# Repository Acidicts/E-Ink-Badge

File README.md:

# E-Ink Badge

A DIY Custom Designed, Monochrome, E-Ink display badge powered by the RP2350A, inspired by the GitHub Universe 2024 conference badge.
~Kinda wanted to see how many words I could describe it with. 

<div style="width:100%; display:inline-flex">

</div>

*(Renders made in Fusion 360)*

<div style="width:100%;">
    <div style="width:100%; display:inline-flex">

    </div>
    <div style="width:100%; display:inline-flex">
        
    </div>
</div>

## Features

- **MCU:** The mighty RP2350A I wish the RP2354A were in stock though
- **Flash:** 16MB onboard but do I want it to remember?
- **Power:** Integrated battery management for a single-cell LiPo, does it charge idk
- **Display:** E-Ink support over SPI, this was painful for part selection
- **Software:** No dedicated firmware/software yet — I'm considering adapting the [Badger 2040](https://github.com/pimoroni/badger2040) software from the GitHub Universe conference badge as a starting point, don't have the time for it

## Build Guide

This board has some fine-pitch and hand-soldering-unfriendly parts (the RP2350A and the E-Ink display's FPC connector), so I'd recommend using a **PCBA service** for the main board rather than hand-soldering it yourself. I know I wouldn't I have tried and failed, mainly cuz I dont have a hotplate.

Most components will already be populated(i liked this fancy word better than `placed`) by the assembly service — you'll only need to install the **battery** and the **display** yourself:

**Bring your own adhesive, please**
~ Not on BOM cuz not required for functionality

1. **Prepare the battery connector:** Trim the battery connector's legs slightly so they don't press against the back of the display once everything is assembled.
2. **Mount the battery:** Apply adhesive to the marked area on the PCB and stick the battery down.
3. **Connect the battery:** Plug the battery cable into the battery connector on the PCB.
4. **Mount the display:** Apply adhesive to the marked area on the front of the PCB and attach the E-Ink display. 
5. **Connect the display cable:** Route the ribbon cable through the indentation/slot in the PCB. Open the FPC connector's clamp arm, insert the ribbon cable, then press the clamp lever back down to lock it in place.

"That's it — the badge is fully assembled", I'd like to say, whether the firmware actually works, is what I'd like to know.

For getting started with software, I'd recommend flashing **CircuitPython**, as it's the easiest way to get up and running. Also have some demo firmware included in this repo, though it's untested/may not work out of the box.

## Firmware

I have some basic firmware in this repo. If you'd like to write your own, here are the SPI pin mappings for the display connection:

### SPI Pinout

| Signal | GPIO |
|--------|------|
| SCLK (Clock)      | GPIO 2 |
| SDI (MOSI/Data)   | GPIO 3 |
| D/C (Data/Command)| GPIO 4 |
| CS (Chip Select)  | GPIO 5 |
| RES (Reset)       | GPIO 6 |
| BUSY              | GPIO 7 |

## Bill of Materials (BOM)

- [Project BOM](./BOM.csv) — full parts list for the badge
- [PCB BOM](./PCB_BOM.md) — parts list specific to the PCB assembly

### AI Usage Declaration 
- In part research
- Part finding (lcsc is hit or miss at finding stuff)
- Firmware Demo creation
- README Build Guide (code completion - fancy autocorrect ig)

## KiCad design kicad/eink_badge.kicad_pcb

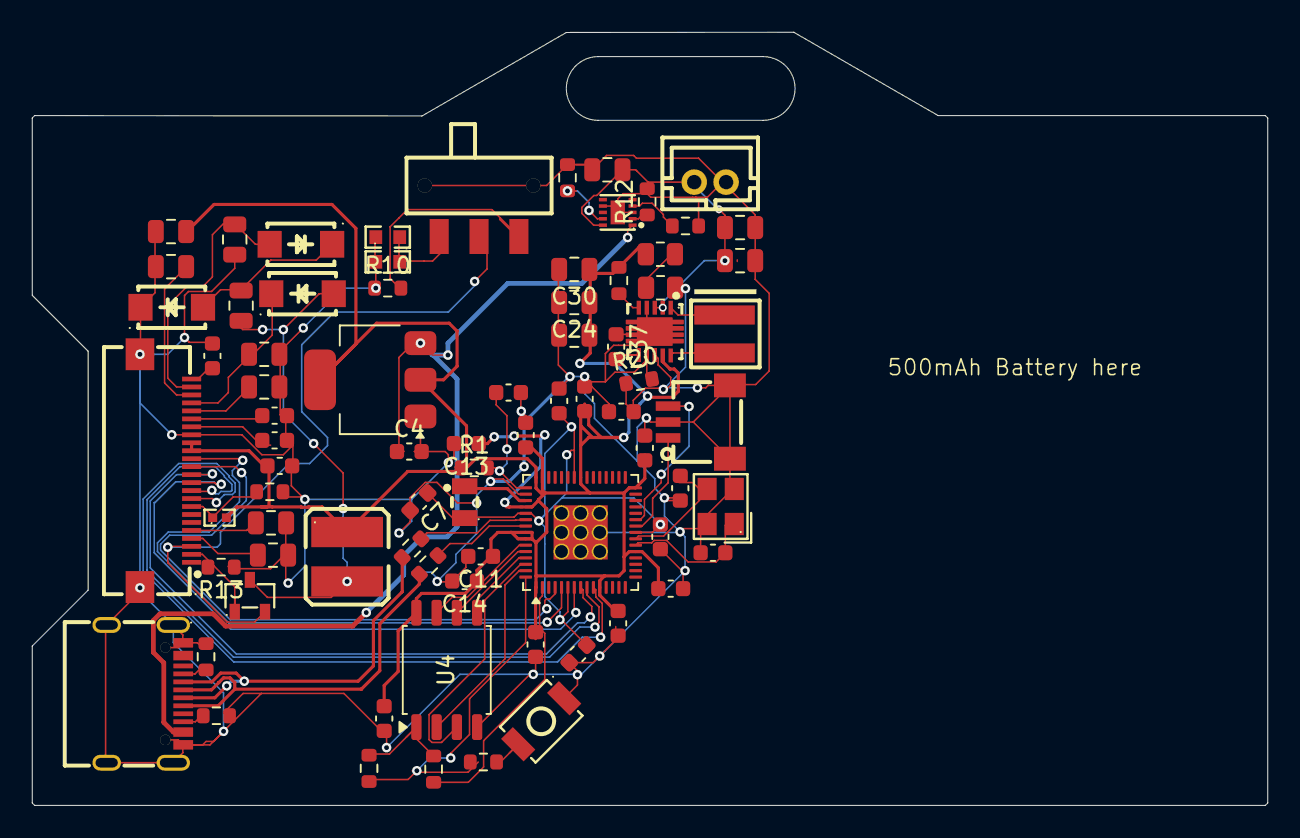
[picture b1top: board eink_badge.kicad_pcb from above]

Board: 2 copper layers, 77.5 x 48.5 mm, 78 parts (0 on the bottom side), 51 nets.

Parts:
C1, C2, C3, C7: 4.7u; C_0603_1608Metric
C4, C5: 10u; C_0603_1608Metric
C6, C8, C9, C10, C11, C12, C13, C14, C15, C16: 100n; C_0603_1608Metric
C17, C18: 15p; C_0603_1608Metric
C19, C20, C21, C22, C23, C25, C26, C27, C29: CL21A475KAQNNNE; C_0805_2012Metric
C24, C30, C35: 22uF; C_0805_2012Metric
C28, C36: 10uF; C_0805_2012Metric
C31, C32, C33, C34: 1uF; C_0603_1608Metric
C37: 0.1uF; C_0603_1608Metric
C38: 10pF; C_0603_1608Metric
CN2: B2B-PH-K-S; CONN-TH_B2B-PH-K-S
D4, D5, D6: SS14; SMA_L4.2-W2.6-LS5.0-RD_1
FPC1: FPC-05FB-24PH20; FPC-SMD_24P-P0.50_FPC-05FB-24PH20
L1: AOTA-B201610S3R3-101-T; IND-SMD_L2.0-W1.6_AOTA-B201610S3R3-101-T
L2: XFL4020-102MEC; IND-SMD_L4.0-W4.0_XFL4020-102MEB
Q1: AO3400A; SOT-23-3_L2.9-W1.3-P1.90-LS2.4-BR
R1: 33; R_0603_1608Metric
R2, R3: 5.1k; R_0603_1608Metric
R4, R5: 27; R_0603_1608Metric
R6: 0; R_0603_1608Metric
R7: DNF; R_0603_1608Metric
R8: 2k; R_0603_1608Metric
R9, R12: 1k; R_0603_1608Metric
R10, R11: 2.2; R_0603_1608Metric
R13, R17: 10k; R_0603_1608Metric
R14: 10k; R0402
R15, R16: 1; R0603
R18: 1M; R_0603_1608Metric
R19, R21: 560k; R_0805_2012Metric
R20: 200k; R_0603_1608Metric
SW1: MST-12D18G2 SMD SLIDE SWITCH; SW-SMD_3P-L9.1-W3.5-P2.50_MST-12D18G2
U1: RP2350A; QFN-60-1EP_7x7mm_P0.4mm_EP3.4x3.4mm
U2: NCP1117-3.3_SOT223; SOT-223-3_TabPin2
U3: GT-USB-7010ASV; USB-C-SMD_G-SWITCH_GT-USB-7010ASV
U4: W25Q128JVS; SOIC-8_5.3x5.3mm_P1.27mm
U5: YZA-009; SW-SMD_YZA-009
U6: ABM8-272-T3_C20625731; CRYSTAL-SMD_4P-L3.2-W2.5-BL
U7: SM03B-SRSS-TB; CONN-SMD_SM03B-SRSS-TB-LF-SN-P
U8: CY43-10UH; IND-SMD_L4.5-W4.0
U9: BQ24040DSQR; WSON-10_L2.0-W2.0-P0.40-BL-EP
U10: TPS63060DSCR; WSON-10_L3.0-W3.0-P0.50-BL-EP-A

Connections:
+1V1: C2.1, C6.1, C7.1, C8.1, L1.1, U1.6 (DVDD), U1.23 (DVDD), U1.39 (DVDD), U1.50 (VREG_FB)
+3V3: C1.1, C5.1, C9.1, C10.1, C11.1, C12.1, C13.1, C14.1, C15.1, C16.1, C24.1, C27.2, C30.1, C34.2, C35.1, FPC1.15, FPC1.16, R1.1, R14.2, R18.1, R21.1, U1.1 (IOVDD), U1.11 (IOVDD), U1.20 (IOVDD), U1.30 (IOVDD), U1.38 (IOVDD), U1.44 (ADC_AVDD), U1.45 (IOVDD), U1.49 (VREG_VIN), U1.53 (USB_OTP_VDD), U1.54 (QSPI_IOVDD), U2.2 (VO), U4.8 (VCC), U8.1, U10.9 (VOUT)
/Battery Charger/Batt+: C23.2, C28.2, C36.2, CN2.2, U9.10 (OUT), U10.2 (VIN), U10.3 (EN)
/E Ink/BS: FPC1.8, R11.1, R14.1
/E Ink/GDR: FPC1.2, Q1.1 (G), R13.2
/E Ink/PREVGH: C20.2, D6.1 (K), FPC1.21
/E Ink/PREVGL: C19.2, D4.2 (A), FPC1.23
/E Ink/RESE: FPC1.3, Q1.2 (S), SW1.2
/E Ink/VCOM: C31.2, FPC1.24
/Root/D+: R5.1, U3.A6 (DP1), U3.B6 (DP2)
/Root/D-: R4.1, U3.A7 (DN1), U3.B7 (DN2)
/Root/GPIO0: R7.1, U1.2 (GPIO0)
/Root/QSPI_SCLK: U1.56 (QSPI_SCLK), U4.6 (CLK)
/Root/QSPI_SD0: U1.57 (QSPI_SD0), U4.5 (DI/IO_{0})
/Root/QSPI_SD1: U1.59 (QSPI_SD1), U4.2 (DO/IO_{1})
/Root/QSPI_SD2: U1.58 (QSPI_SD2), U4.3 (~WP/IO_{2})
/Root/QSPI_SD3: U1.55 (QSPI_SD3), U4.7 (~HOLD/~RESET/IO_{3})
/Root/QSPI_SS: R6.1, R9.2, U1.60 (~QSPI_SS)
/Root/SWCLK: U1.24 (SWCLK), U7.1
/Root/SWDIO: U1.25 (SWDIO), U7.3
/Root/VREG_AVDD: C3.1, R1.2, U1.46 (VREG_AVDD)
/Root/VREG_LX: L1.2, U1.48 (VREG_LX)
/Root/XIN: C18.2, U1.21 (XIN), U6.1
/Root/XOUT: C17.2, U1.22 (XOUT), U6.3
GND: C1.2, C2.2, C3.2, C4.2, C5.2, C6.2, C7.2, C8.2, C9.2, C10.2, C11.2, C12.2, C13.2, C14.2, C15.2, C16.2, C17.1, C18.1, C19.1, C20.1, C22.2, C23.1, C24.2, C25.1, C26.1, C27.1, C28.1, C29.2, C30.2, C31.1, C32.1, C33.1, C34.1, C35.2, C36.1, C37.1, C38.1, CN2.1, D5.1 (K), FPC1.17, FPC1.25, FPC1.26, R2.2, R3.2, R8.2, R10.1, R11.2, R12.2, R13.1, R15.1, R16.1, R17.2, R20.2, U1.47 (VREG_PGND), U1.61 (GND), U2.1 (GND), U3.1 (SHELL), U3.2 (SHELL), U3.3 (SHELL), U3.4 (SHELL), U3.A1B12 (GND), U3.B1A12 (GND), U4.4 (GND), U5.1, U6.2 (GND), U6.4 (GND), U7.2, U7.4, U7.5, U9.3 (VSS), U9.7 (ISET2), U9.11 (EP), U10.4 (PS/SYNC), U10.7 (GND), U10.11 (PAD)
unnamed: C22.1, FPC1.5
unnamed: C25.2, FPC1.22
unnamed: C26.2, FPC1.20
unnamed: C29.1, FPC1.4
unnamed: C32.2, FPC1.19
unnamed: C33.2, FPC1.18
unnamed: C21.2, D4.1 (K), D5.2 (A)
unnamed: C21.1, D6.2 (A), Q1.3 (D), U8.2
unnamed: R9.1, U5.2
unnamed: R10.2, SW1.3
unnamed: R15.2, R16.2, SW1.1
unnamed: R19.1, R21.2
unnamed: R4.2, U1.51 (USB_DM)
unnamed: R5.2, U1.52 (USB_DP)
unnamed: C4.1, U2.3 (VI)
unnamed: R3.1, U3.A5 (CC1)
unnamed: R2.1, U3.B5 (CC2)
unnamed: R6.2, R7.2, U4.1 (~CS)
unnamed: R12.1, U9.2 (ISET)
unnamed: R8.1, U9.4 (PRETERM)
unnamed: R17.1, U9.9 (TS)
unnamed: C38.2, R19.2, R20.1, U10.8 (FB)
unnamed: L2.1, U10.1 (L1)
unnamed: L2.2, U10.10 (L2)
unnamed: R18.2, U10.5 (PG)
unnamed: C37.2, U10.6 (VAUX)

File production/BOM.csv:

Designator,Footprint,Quantity,Value,LCSC Part #
"C1, C2, C3, C7",0603,4,4.7u,
"C10, C11, C12, C13, C14, C15, C16, C6, C8, C9",0603,10,100n,
"C17, C18",0603,2,15p,
"C19, C20, C21, C22, C23, C25, C26, C27, C29",0805,9,CL21A475KAQNNNE,C1779
"C24, C30, C35",0805,3,22uF,C92814
"C28, C36",0805,2,10uF,C87157
"C31, C32, C33, C34",0603,4,1uF,C15849
C37,0603,1,0.1uF,
C38,0603,1,10pF,C1634
"C4, C5",0603,2,10u,
CN2,CONN-TH_B2B-PH-K-S,1,B2B-PH-K-S,C131337
"D4, D5, D6",SMA_L4.2-W2.6-LS5.0-RD_1,3,SS14,C2480
FPC1,FPC-SMD_24P-P0.50_FPC-05FB-24PH20,1,FPC-05FB-24PH20,C2856831
L1,IND-SMD_L2.0-W1.6_AOTA-B201610S3R3-101-T,1,AOTA-B201610S3R3-101-T,C42411119
L2,IND-SMD_L4.0-W4.0_XFL4020-102MEB,1,XFL4020-102MEC,C5355380
Q1,SOT-23-3_L2.9-W1.3-P1.90-LS2.4-BR,1,AO3400A,C20917
R1,0603,1,33,
"R10, R11",0603,2,2.2,C22939
"R12, R9",0603,2,1k,
R13,0603,1,10k,C115324
R14,R0402,1,10k,C25744
"R15, R16",R0603,2,1,C22936
R17,0603,1,10k,C98220
R18,0603,1,1M,C105578
"R19, R21",0805,2,560k,C2933556
"R2, R3",0603,2,5.1k,
R20,0603,1,200k,C105574
"R4, R5",0603,2,27,
R6,0603,1,0,
R7,0603,1,DNF,
R8,0603,1,2k,C140173
SW1,SW-SMD_3P-L9.1-W3.5-P2.50_MST-12D18G2,1,MST-12D18G2 SMD SLIDE SWITCH,C49023765
U1,QFN-60-1EP_7x7mm_P0.4mm_EP3.4x3.4mm,1,RP2350A,C42411118
U10,WSON-10_L3.0-W3.0-P0.50-BL-EP-A,1,TPS63060DSCR,C48567
U2,SOT-223-3_TabPin2,1,NCP1117-3.3_SOT223,
U3,USB-C-SMD_G-SWITCH_GT-USB-7010ASV,1,GT-USB-7010ASV,C2988369
U4,SOIC-8_5.3x5.3mm_P1.27mm,1,W25Q128JVS,
U5,SW-SMD_YZA-009,1,YZA-009,C49108621
U6,CRYSTAL-SMD_4P-L3.2-W2.5-BL,1,ABM8-272-T3_C20625731,C20625731
U7,CONN-SMD_SM03B-SRSS-TB-LF-SN-P,1,SM03B-SRSS-TB,C160403
U8,IND-SMD_L4.5-W4.0,1,CY43-10UH,C2929419
U9,WSON-10_L2.0-W2.0-P0.40-BL-EP,1,BQ24040DSQR,C81080

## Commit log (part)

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2026-05-10 Repo Refactoring
2026-05-11 Refactor code structure for improved readability and maintainability
2026-05-11 Fix layout issues in README.md by updating display styles for images
2026-05-11 Fix image display width in README.md for better layout consistency
